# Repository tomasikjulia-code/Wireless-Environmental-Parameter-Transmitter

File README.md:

# Wireless Environmental Parameter Transmitter

A professional, compact IoT solution for high-precision environmental monitoring based on the **ESP32-C3** (RISC-V) architecture. This project integrates sensing, power management, and local visualization into a single PCB.

---

## Overview

This device is designed to measure, display, and transmit environmental data (Temperature & Humidity) over Wi-Fi or Bluetooth LE. It features a robust power circuit, making it suitable for battery-operated remote applications.

### Key Features
* **Microcontroller:** ESP32-C3 with 2.4GHz Wi-Fi and BLE 5.0.
* **High-Precision Sensing:** Integrated **SHT45** sensor for accurate climate data.
* **Display Support:** Dedicated I2C header for OLED displays (SSD1306/SH1106).
* **Power System:** USB-C connectivity for power and programming.
    * Li-ion/Li-Po battery charging via **NCP73831**.
    * Battery voltage sensing for level monitoring.
* **User Interface:** Physical buttons for `Reset` and `Boot`.

---

## Hardware Specifications

The schematic was developed using **KiCad 9.0**. Key circuit blocks include:

* **RF Section:** Optimized antenna matching network for the 2.4GHz band.
* **Power Rail:** Stable 3.3V LDO regulator with decoupling capacitors for noise reduction.
* **Protection:** ESD protection on the USB-C data lines (D+/D-).
* **Flash Memory:** External SPI Flash for extended data logging or complex firmware.

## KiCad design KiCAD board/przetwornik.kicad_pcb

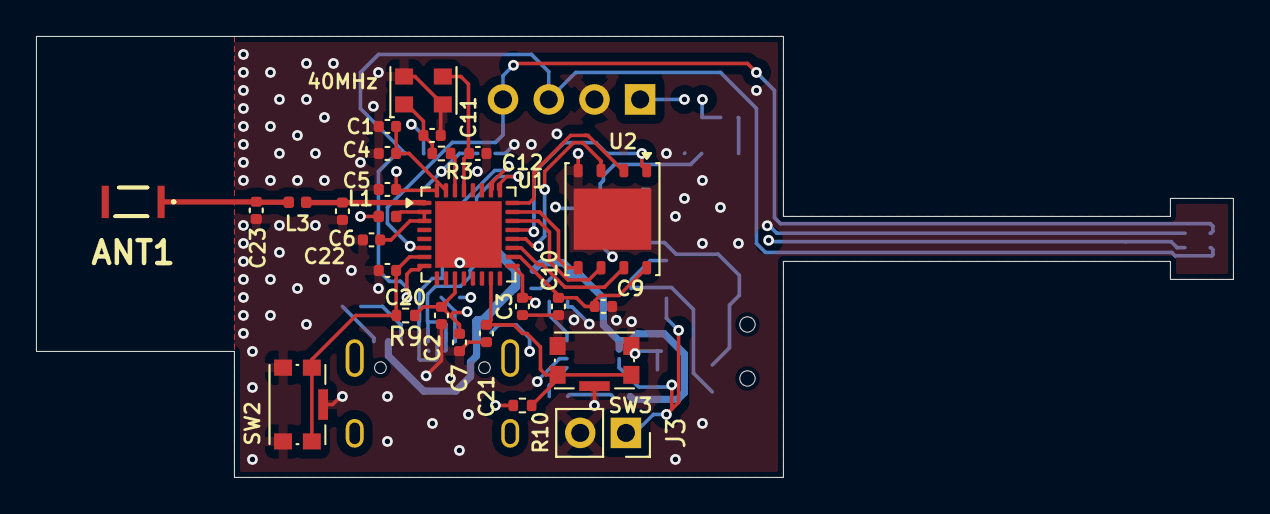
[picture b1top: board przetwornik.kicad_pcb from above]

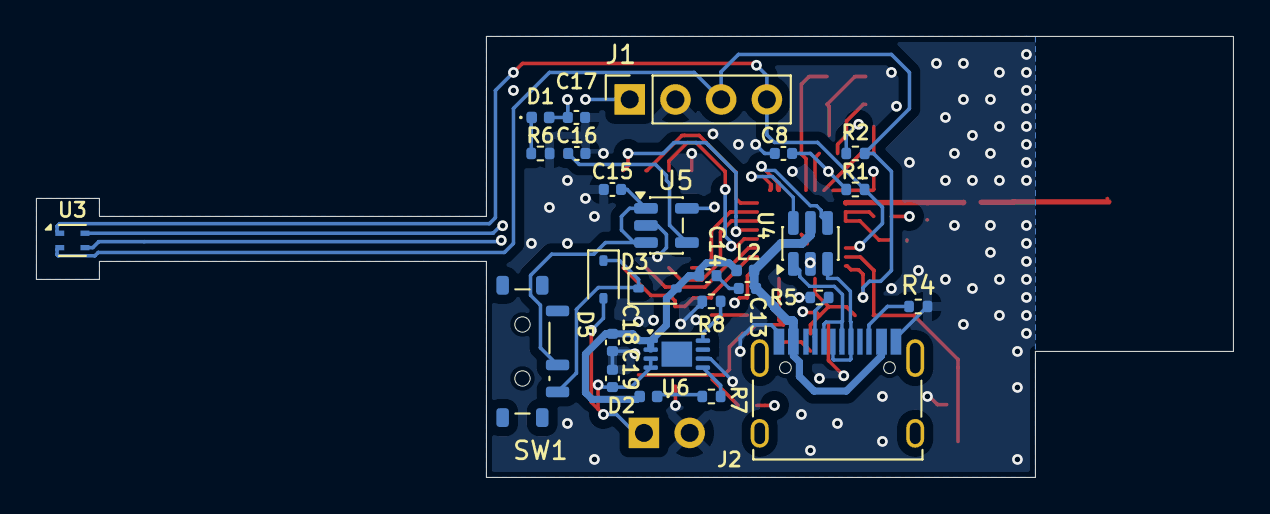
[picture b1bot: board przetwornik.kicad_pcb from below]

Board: 4 copper layers, 66.5 x 24.5 mm, 54 parts (27 on the bottom side), 36 nets.

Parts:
40MHz: 40MHz; Oscillator_SMD_EuroQuartz_XO32-4Pin_3.2x2.5mm
ANT1: ANT3216LL00R2400A
C1, C7, C9, C15, C17: 10u; C_0402_1005Metric
C2, C3, C4, C5, C6, C8, C10, C13, C14, C16, C20, C21: 100n; C_0402_1005Metric
C11, C12: 10p; C_0402_1005Metric
C18, C19: 4.7u; C_0402_1005Metric
C22, C23: 3p3; C_0402_1005Metric
D1, D2: LED; LED_0402_1005Metric
D3, D5: B0540WS; D_SOD-323
J1: 1x4 socket; PinSocket_1x04_P2.54mm_Vertical
J2: USB_C_Receptacle_USB2.0_14P; USB_C_Receptacle_HRO_TYPE-C-31-M-12
J3: 1x2 socket; PinSocket_1x02_P2.54mm_Vertical
L1, L2, L3: 2n2; L_0402_1005Metric
R1, R2: 4.7k; R_0402_1005Metric
R3: 22k; R_0402_1005Metric
R4, R5, R9, R10: 5k1; R_0402_1005Metric
R6: 1k; R_0402_1005Metric
R7: 470R; R_0402_1005Metric
R8: 2k; R_0402_1005Metric
SW1: SW_SPDT_MSM; SW_SPDT_Shouhan_MSK12C02
SW2, SW3: SW_Push; SW_Push_1P1T-SH_NO_CK_KMR2xxG
U1: ESP32-C3; QFN-32-1EP_5x5mm_P0.5mm_EP3.7x3.7mm
U2: W25Q32JVZP; WSON-8-1EP_6x5mm_P1.27mm_EP3.4x4.3mm
U3: SHT4x; Sensirion_DFN-4_1.5x1.5mm_P0.8mm_SHT4x_NoCentralPad
U4: USBLC6-2SC6; SOT-23-6
U5: SPX3819M5-L-3-3; SOT-23-5
U6: MCP73831-2-MC; DFN-8-1EP_3x2mm_P0.5mm_EP1.7x1.4mm

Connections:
+3.3V: C1.2, C2.2, C3.2, C4.2, C5.2, C7.2, C8.2, C17.1, D1.2 (A), J1.1, L1.1, R1.1, R2.1, R9.1, R10.1, U1.11 (VDD3P3_RTC), U1.17 (VDD3P3_CPU), U1.31 (VDDA), U1.32 (VDDA), U3.3 (VDD), U5.5 (OUT)
/D+: J2.A6 (D+), J2.B6 (D+), U4.3 (I/O2)
/D-: J2.A7 (D-), J2.B7 (D-), U4.1 (I/O1)
ANTHENA: C22.1, L3.1, U1.1 (LNA_IN)
Acc: C19.1, D5.2 (A), J3.1, U6.3 (V_{BAT}), U6.4 (V_{BAT})
BOOT: C21.1, R10.2, SW3.1, U1.15 (GPIO9)
CHIP_EN: C20.1, R9.2, SW2.1, U1.7 (CHIP_EN)
D_N: U1.25 (GPIO18), U4.6 (I/O1)
D_P: U1.26 (GPIO19), U4.4 (I/O2)
GND: 40MHz.2 (G), 40MHz.4 (G), C1.1, C2.1, C3.1, C4.1, C5.1, C6.1, C7.1, C8.1, C9.1, C10.1, C11.2, C12.2, C15.2, C16.2, C17.2, C18.2, C19.2, C20.2, C21.2, C22.2, C23.2, J1.2, J2.A1 (GND), J2.A12 (GND), J2.B1 (GND), J2.B12 (GND), J3.2, R4.2, R5.2, R6.2, R8.1, SW2.2, SW2.SH, SW3.2, SW3.SH, U1.33 (GND), U2.4 (GND), U2.9 (EP), U3.4 (VSS), U4.2 (GND), U5.2 (GND), U6.6 (V_{SS})
unnamed: ANT1.1, C23.1, L3.2
unnamed: C6.2, L1.2, U1.2 (VDD3P3), U1.3 (VDD3P3)
unnamed: C13.2, C14.2
unnamed: D1.1 (K), R6.1
unnamed: D2.1 (K), R7.1
unnamed: D3.1 (K), D5.1 (K), SW1.3 (4)
unnamed: J2.A5 (CC1), R5.1
unnamed: J2.B5 (CC2), R4.1
unnamed: C15.1, SW1.2 (3), U5.1 (IN), U5.3 (EN)
unnamed: R3.2, U1.30 (XTAL_P)
unnamed: C16.1, U5.4 (BP)
unnamed: R8.2, U6.8 (PROG)
unnamed: R7.2, U6.5 (STAT)
SCL: J1.3, R2.2, U1.8 (GPIO3), U3.2 (SCL)
SDA: J1.4, R1.2, U1.6 (GPIO2), U3.1 (SDA)
SPI_CLK: U1.22 (SPICLK), U2.6 (CLK)
SPI_CS: U1.21 (SPICS0), U2.1 (~CS)
SPI_D0: U1.24 (SPIQ), U2.2 (DO/IO_{1})
SPI_DI: U1.23 (SPID), U2.5 (DI/IO_{0})
SPI_HOLD: U1.19 (SPIHD), U2.7 (~HOLD/~RESET/IO_{3})
SPI_WP: U1.20 (SPIWP), U2.3 (~WP/IO_{2})
VBUS: C13.1, J2.A4 (VBUS), J2.A9 (VBUS), J2.B4 (VBUS), J2.B9 (VBUS), L2.1, U4.5 (VBUS)
VBUS_FILT: C14.1, C18.1, D2.2 (A), D3.2 (A), L2.2, U6.1 (V_{DD}), U6.2 (V_{DD})
VCC_SPI: C9.2, C10.2, U1.18 (VDD_SPI), U2.8 (VCC)
XTAL_N: 40MHz.3, C12.1, U1.29 (XTAL_N)
XTAL_P: 40MHz.1, C11.1, R3.1

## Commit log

2026-02-18 KiCAD files
2026-02-18 kicad
2026-02-18 photos of project
2026-02-18 Gerber files
2026-02-18 software
